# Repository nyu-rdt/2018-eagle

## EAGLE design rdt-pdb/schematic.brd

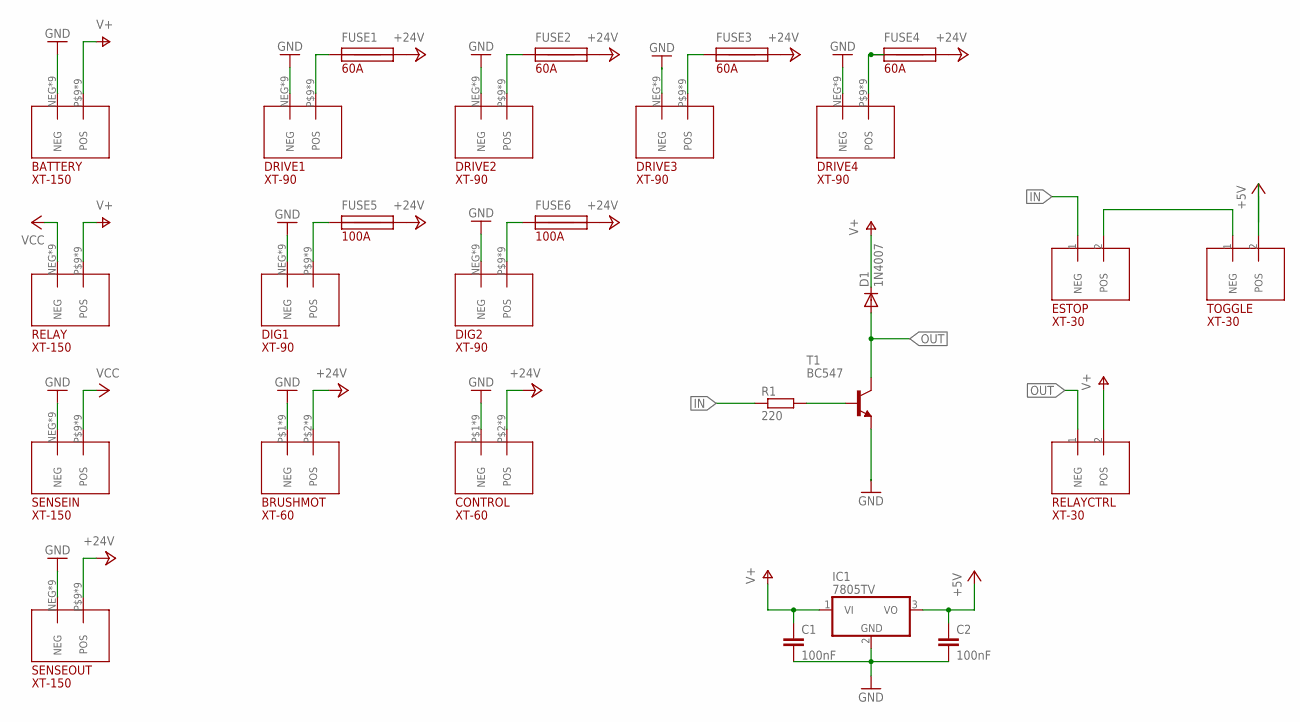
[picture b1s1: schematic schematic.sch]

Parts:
BATTERY: XT-150
BRUSHMOT: XT-60
C1, C2: 100nF; C5B5
CONTROL: XT-60
D1: 1N4007; DO41-10
DIG1, DIG2: XT-90
DRIVE1, DRIVE2, DRIVE3, DRIVE4: XT-90
ESTOP: XT-30
FUSE1, FUSE2, FUSE3, FUSE4: 60A; 3555
FUSE5, FUSE6: 100A; 3555
IC1: 7805TV; TO220V
R1: 220; 0204/7
RELAY: XT-150
RELAYCTRL: XT-30
SENSEIN: XT-150
SENSEOUT: XT-150
T1: BC547; TO92
TOGGLE: XT-30

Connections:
+5V: C2.1, IC1.3 (VO), TOGGLE.2 (POS)
+24V: BRUSHMOT.P$2 (POS), BRUSHMOT.P$7 (POS), BRUSHMOT.P$8 (POS), BRUSHMOT.P$9 (POS), BRUSHMOT.P$10 (POS), BRUSHMOT.P$11 (POS), BRUSHMOT.P$12 (POS), BRUSHMOT.P$13 (POS), BRUSHMOT.P$14 (POS), CONTROL.P$2 (POS), CONTROL.P$7 (POS), CONTROL.P$8 (POS), CONTROL.P$9 (POS), CONTROL.P$10 (POS), CONTROL.P$11 (POS), CONTROL.P$12 (POS), CONTROL.P$13 (POS), CONTROL.P$14 (POS), FUSE1.P$3, FUSE1.P$4, FUSE2.P$3, FUSE2.P$4, FUSE3.P$3, FUSE3.P$4, FUSE4.P$3, FUSE4.P$4, FUSE5.P$3, FUSE5.P$4, FUSE6.P$3, FUSE6.P$4, SENSEOUT.P$9 (POS), SENSEOUT.P$10 (POS), SENSEOUT.P$11 (POS), SENSEOUT.P$12 (POS), SENSEOUT.P$13 (POS), SENSEOUT.P$14 (POS), SENSEOUT.P$15 (POS), SENSEOUT.P$16 (POS), SENSEOUT.POS
GND: BATTERY.NEG, BATTERY.P$1 (NEG), BATTERY.P$2 (NEG), BATTERY.P$3 (NEG), BATTERY.P$4 (NEG), BATTERY.P$5 (NEG), BATTERY.P$6 (NEG), BATTERY.P$7 (NEG), BATTERY.P$8 (NEG), BRUSHMOT.P$1 (NEG), BRUSHMOT.P$3 (NEG), BRUSHMOT.P$4 (NEG), BRUSHMOT.P$5 (NEG), BRUSHMOT.P$6 (NEG), BRUSHMOT.P$15 (NEG), BRUSHMOT.P$16 (NEG), BRUSHMOT.P$17 (NEG), BRUSHMOT.P$18 (NEG), C1.2, C2.2, CONTROL.P$1 (NEG), CONTROL.P$3 (NEG), CONTROL.P$4 (NEG), CONTROL.P$5 (NEG), CONTROL.P$6 (NEG), CONTROL.P$15 (NEG), CONTROL.P$16 (NEG), CONTROL.P$17 (NEG), CONTROL.P$18 (NEG), DIG1.NEG, DIG1.P$1 (NEG), DIG1.P$2 (NEG), DIG1.P$3 (NEG), DIG1.P$4 (NEG), DIG1.P$5 (NEG), DIG1.P$6 (NEG), DIG1.P$7 (NEG), DIG1.P$8 (NEG), DIG2.NEG, DIG2.P$1 (NEG), DIG2.P$2 (NEG), DIG2.P$3 (NEG), DIG2.P$4 (NEG), DIG2.P$5 (NEG), DIG2.P$6 (NEG), DIG2.P$7 (NEG), DIG2.P$8 (NEG), DRIVE1.NEG, DRIVE1.P$1 (NEG), DRIVE1.P$2 (NEG), DRIVE1.P$3 (NEG), DRIVE1.P$4 (NEG), DRIVE1.P$5 (NEG), DRIVE1.P$6 (NEG), DRIVE1.P$7 (NEG), DRIVE1.P$8 (NEG), DRIVE2.NEG, DRIVE2.P$1 (NEG), DRIVE2.P$2 (NEG), DRIVE2.P$3 (NEG), DRIVE2.P$4 (NEG), DRIVE2.P$5 (NEG), DRIVE2.P$6 (NEG), DRIVE2.P$7 (NEG), DRIVE2.P$8 (NEG), DRIVE3.NEG, DRIVE3.P$1 (NEG), DRIVE3.P$2 (NEG), DRIVE3.P$3 (NEG), DRIVE3.P$4 (NEG), DRIVE3.P$5 (NEG), DRIVE3.P$6 (NEG), DRIVE3.P$7 (NEG), DRIVE3.P$8 (NEG), DRIVE4.NEG, DRIVE4.P$1 (NEG), DRIVE4.P$2 (NEG), DRIVE4.P$3 (NEG), DRIVE4.P$4 (NEG), DRIVE4.P$5 (NEG), DRIVE4.P$6 (NEG), DRIVE4.P$7 (NEG), DRIVE4.P$8 (NEG), IC1.2 (GND), SENSEIN.NEG, SENSEIN.P$1 (NEG), SENSEIN.P$2 (NEG), SENSEIN.P$3 (NEG), SENSEIN.P$4 (NEG), SENSEIN.P$5 (NEG), SENSEIN.P$6 (NEG), SENSEIN.P$7 (NEG), SENSEIN.P$8 (NEG), SENSEOUT.NEG, SENSEOUT.P$1 (NEG), SENSEOUT.P$2 (NEG), SENSEOUT.P$3 (NEG), SENSEOUT.P$4 (NEG), SENSEOUT.P$5 (NEG), SENSEOUT.P$6 (NEG), SENSEOUT.P$7 (NEG), SENSEOUT.P$8 (NEG), T1.1 (E)
IN: ESTOP.1 (NEG), R1.1
unnamed: ESTOP.2 (POS), TOGGLE.1 (NEG)
unnamed: DIG2.P$9 (POS), DIG2.P$10 (POS), DIG2.P$11 (POS), DIG2.P$12 (POS), DIG2.P$13 (POS), DIG2.P$14 (POS), DIG2.P$15 (POS), DIG2.P$16 (POS), DIG2.POS, FUSE6.P$1, FUSE6.P$2
unnamed: DIG1.P$9 (POS), DIG1.P$10 (POS), DIG1.P$11 (POS), DIG1.P$12 (POS), DIG1.P$13 (POS), DIG1.P$14 (POS), DIG1.P$15 (POS), DIG1.P$16 (POS), DIG1.POS, FUSE5.P$1, FUSE5.P$2
unnamed: DRIVE1.P$9 (POS), DRIVE1.P$10 (POS), DRIVE1.P$11 (POS), DRIVE1.P$12 (POS), DRIVE1.P$13 (POS), DRIVE1.P$14 (POS), DRIVE1.P$15 (POS), DRIVE1.P$16 (POS), DRIVE1.POS, FUSE1.P$1, FUSE1.P$2
unnamed: DRIVE2.P$9 (POS), DRIVE2.P$10 (POS), DRIVE2.P$11 (POS), DRIVE2.P$12 (POS), DRIVE2.P$13 (POS), DRIVE2.P$14 (POS), DRIVE2.P$15 (POS), DRIVE2.P$16 (POS), DRIVE2.POS, FUSE2.P$1, FUSE2.P$2
unnamed: DRIVE3.P$9 (POS), DRIVE3.P$10 (POS), DRIVE3.P$11 (POS), DRIVE3.P$12 (POS), DRIVE3.P$13 (POS), DRIVE3.P$14 (POS), DRIVE3.P$15 (POS), DRIVE3.P$16 (POS), DRIVE3.POS, FUSE3.P$1, FUSE3.P$2
unnamed: DRIVE4.P$9 (POS), DRIVE4.P$10 (POS), DRIVE4.P$11 (POS), DRIVE4.P$12 (POS), DRIVE4.P$13 (POS), DRIVE4.P$14 (POS), DRIVE4.P$15 (POS), DRIVE4.P$16 (POS), DRIVE4.POS, FUSE4.P$1, FUSE4.P$2
unnamed: R1.2, T1.2 (B)
OUT: D1.A, RELAYCTRL.1 (NEG), T1.3 (C)
V+: BATTERY.P$9 (POS), BATTERY.P$10 (POS), BATTERY.P$11 (POS), BATTERY.P$12 (POS), BATTERY.P$13 (POS), BATTERY.P$14 (POS), BATTERY.P$15 (POS), BATTERY.P$16 (POS), BATTERY.POS, C1.1, D1.C, IC1.1 (VI), RELAY.P$9 (POS), RELAY.P$10 (POS), RELAY.P$11 (POS), RELAY.P$12 (POS), RELAY.P$13 (POS), RELAY.P$14 (POS), RELAY.P$15 (POS), RELAY.P$16 (POS), RELAY.POS, RELAYCTRL.2 (POS)
VCC: RELAY.NEG, RELAY.P$1 (NEG), RELAY.P$2 (NEG), RELAY.P$3 (NEG), RELAY.P$4 (NEG), RELAY.P$5 (NEG), RELAY.P$6 (NEG), RELAY.P$7 (NEG), RELAY.P$8 (NEG), SENSEIN.P$9 (POS), SENSEIN.P$10 (POS), SENSEIN.P$11 (POS), SENSEIN.P$12 (POS), SENSEIN.P$13 (POS), SENSEIN.P$14 (POS), SENSEIN.P$15 (POS), SENSEIN.P$16 (POS), SENSEIN.POS

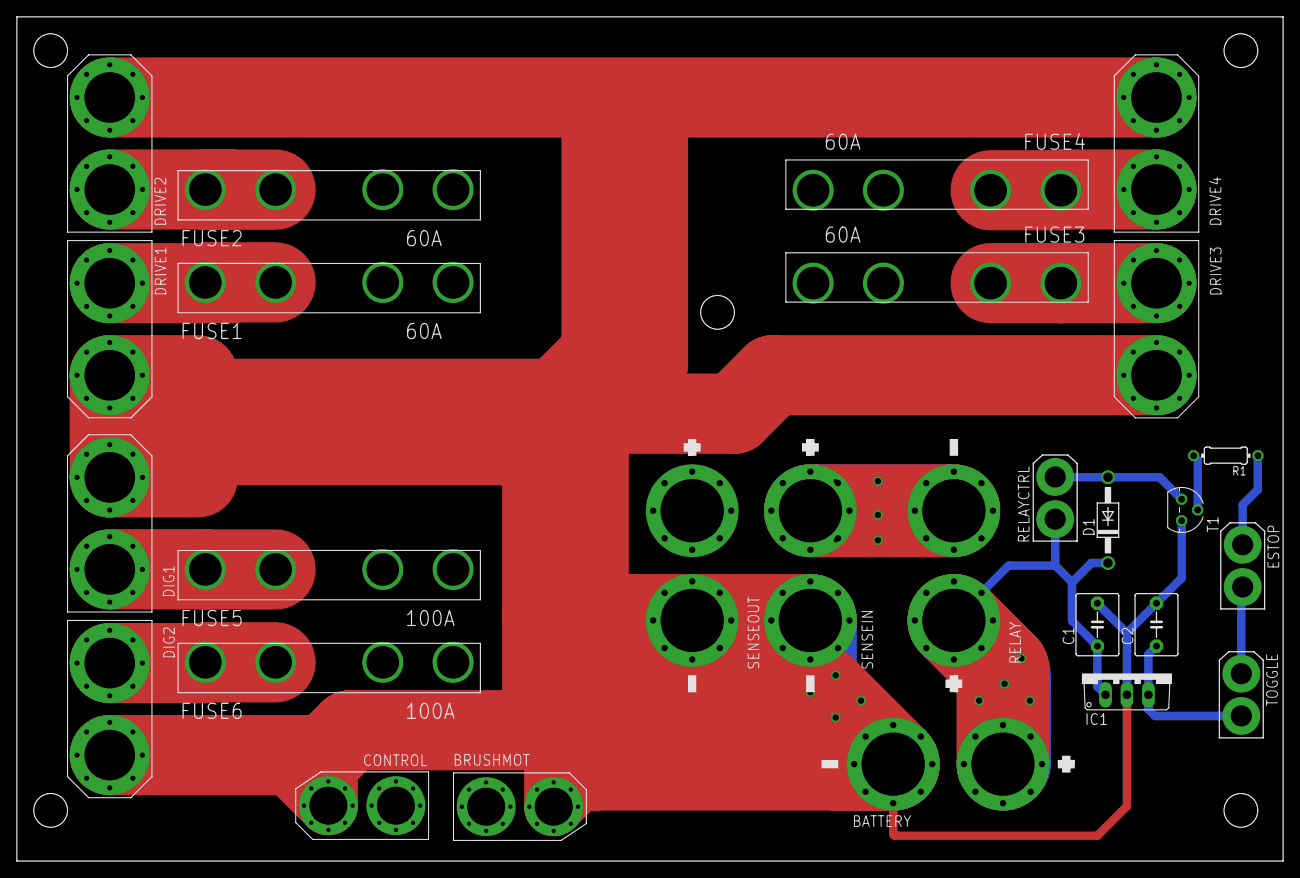
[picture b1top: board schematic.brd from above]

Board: 2 copper layers, 150.0 x 100.0 mm, 27 parts (0 on the bottom side), 15 nets.

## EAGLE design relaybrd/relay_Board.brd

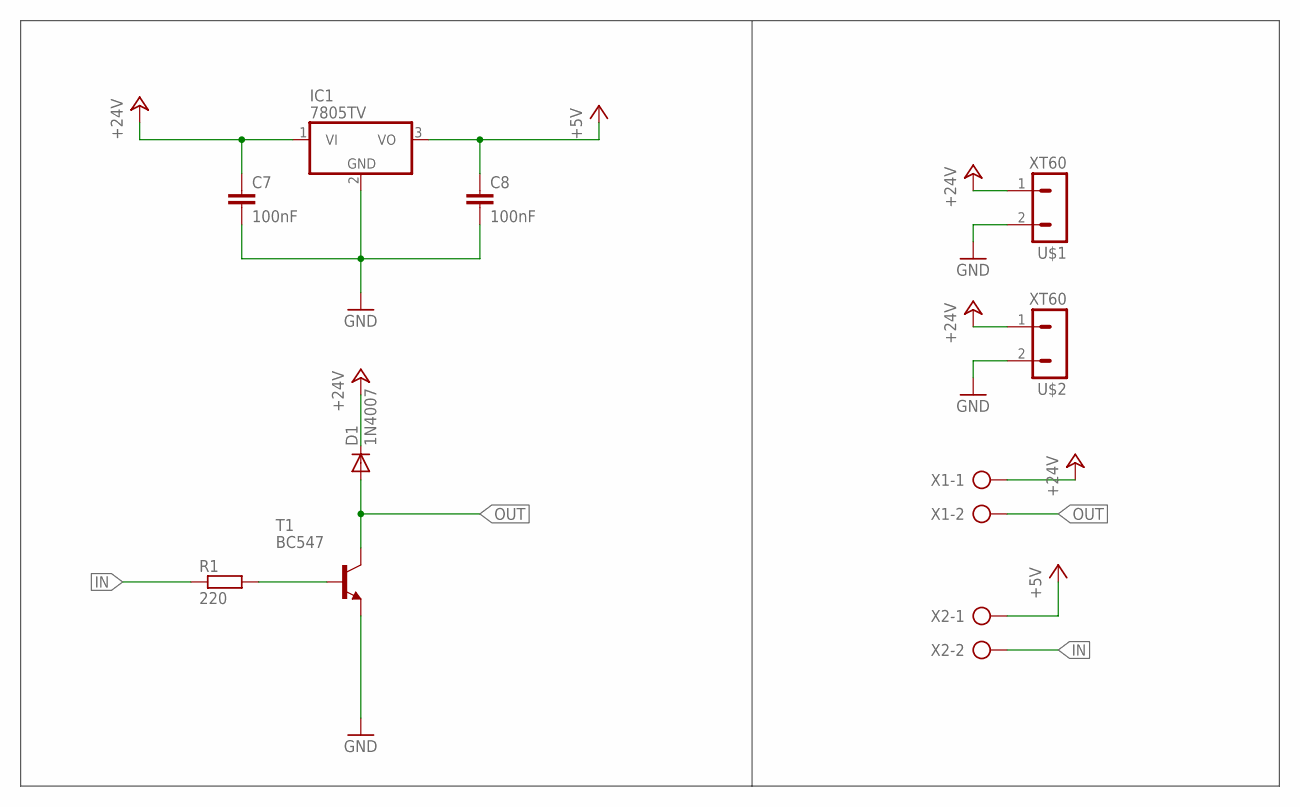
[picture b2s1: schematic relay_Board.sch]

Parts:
C7, C8: 100nF; C5B5
D1: 1N4007; DIODE
IC1: 7805TV; TO220V
R1: 220; 0207/10
T1: BC547; TO92
U$1, U$2: XT60
X1, X2: AK500/2

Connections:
+5V: C8.1, IC1.3 (VO), X2.1
+24V: C7.1, D1.C, IC1.1 (VI), U$1.1, U$2.1, X1.1
GND: C7.2, C8.2, IC1.2 (GND), T1.1 (E), U$1.2, U$2.2
IN: R1.1, X2.2
unnamed: R1.2, T1.2 (B)
OUT: D1.A, T1.3 (C), X1.2

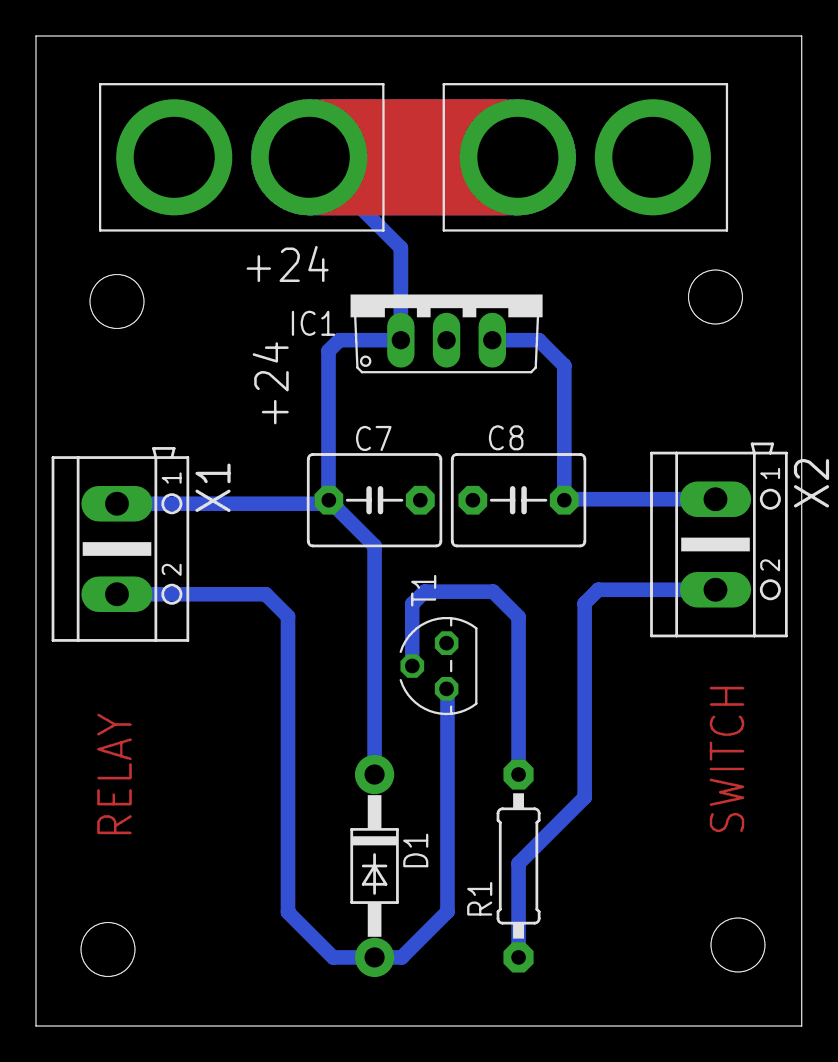
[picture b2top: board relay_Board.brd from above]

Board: 2 copper layers, 42.5 x 55.0 mm, 10 parts (0 on the bottom side), 6 nets.

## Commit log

2019-03-15 Change size and spacing
